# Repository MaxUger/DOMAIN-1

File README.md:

# DOMAIN-1
 Full size keyboard with two additional upper rows.
 
 Main Board:

Daughter Board / Upper Board:

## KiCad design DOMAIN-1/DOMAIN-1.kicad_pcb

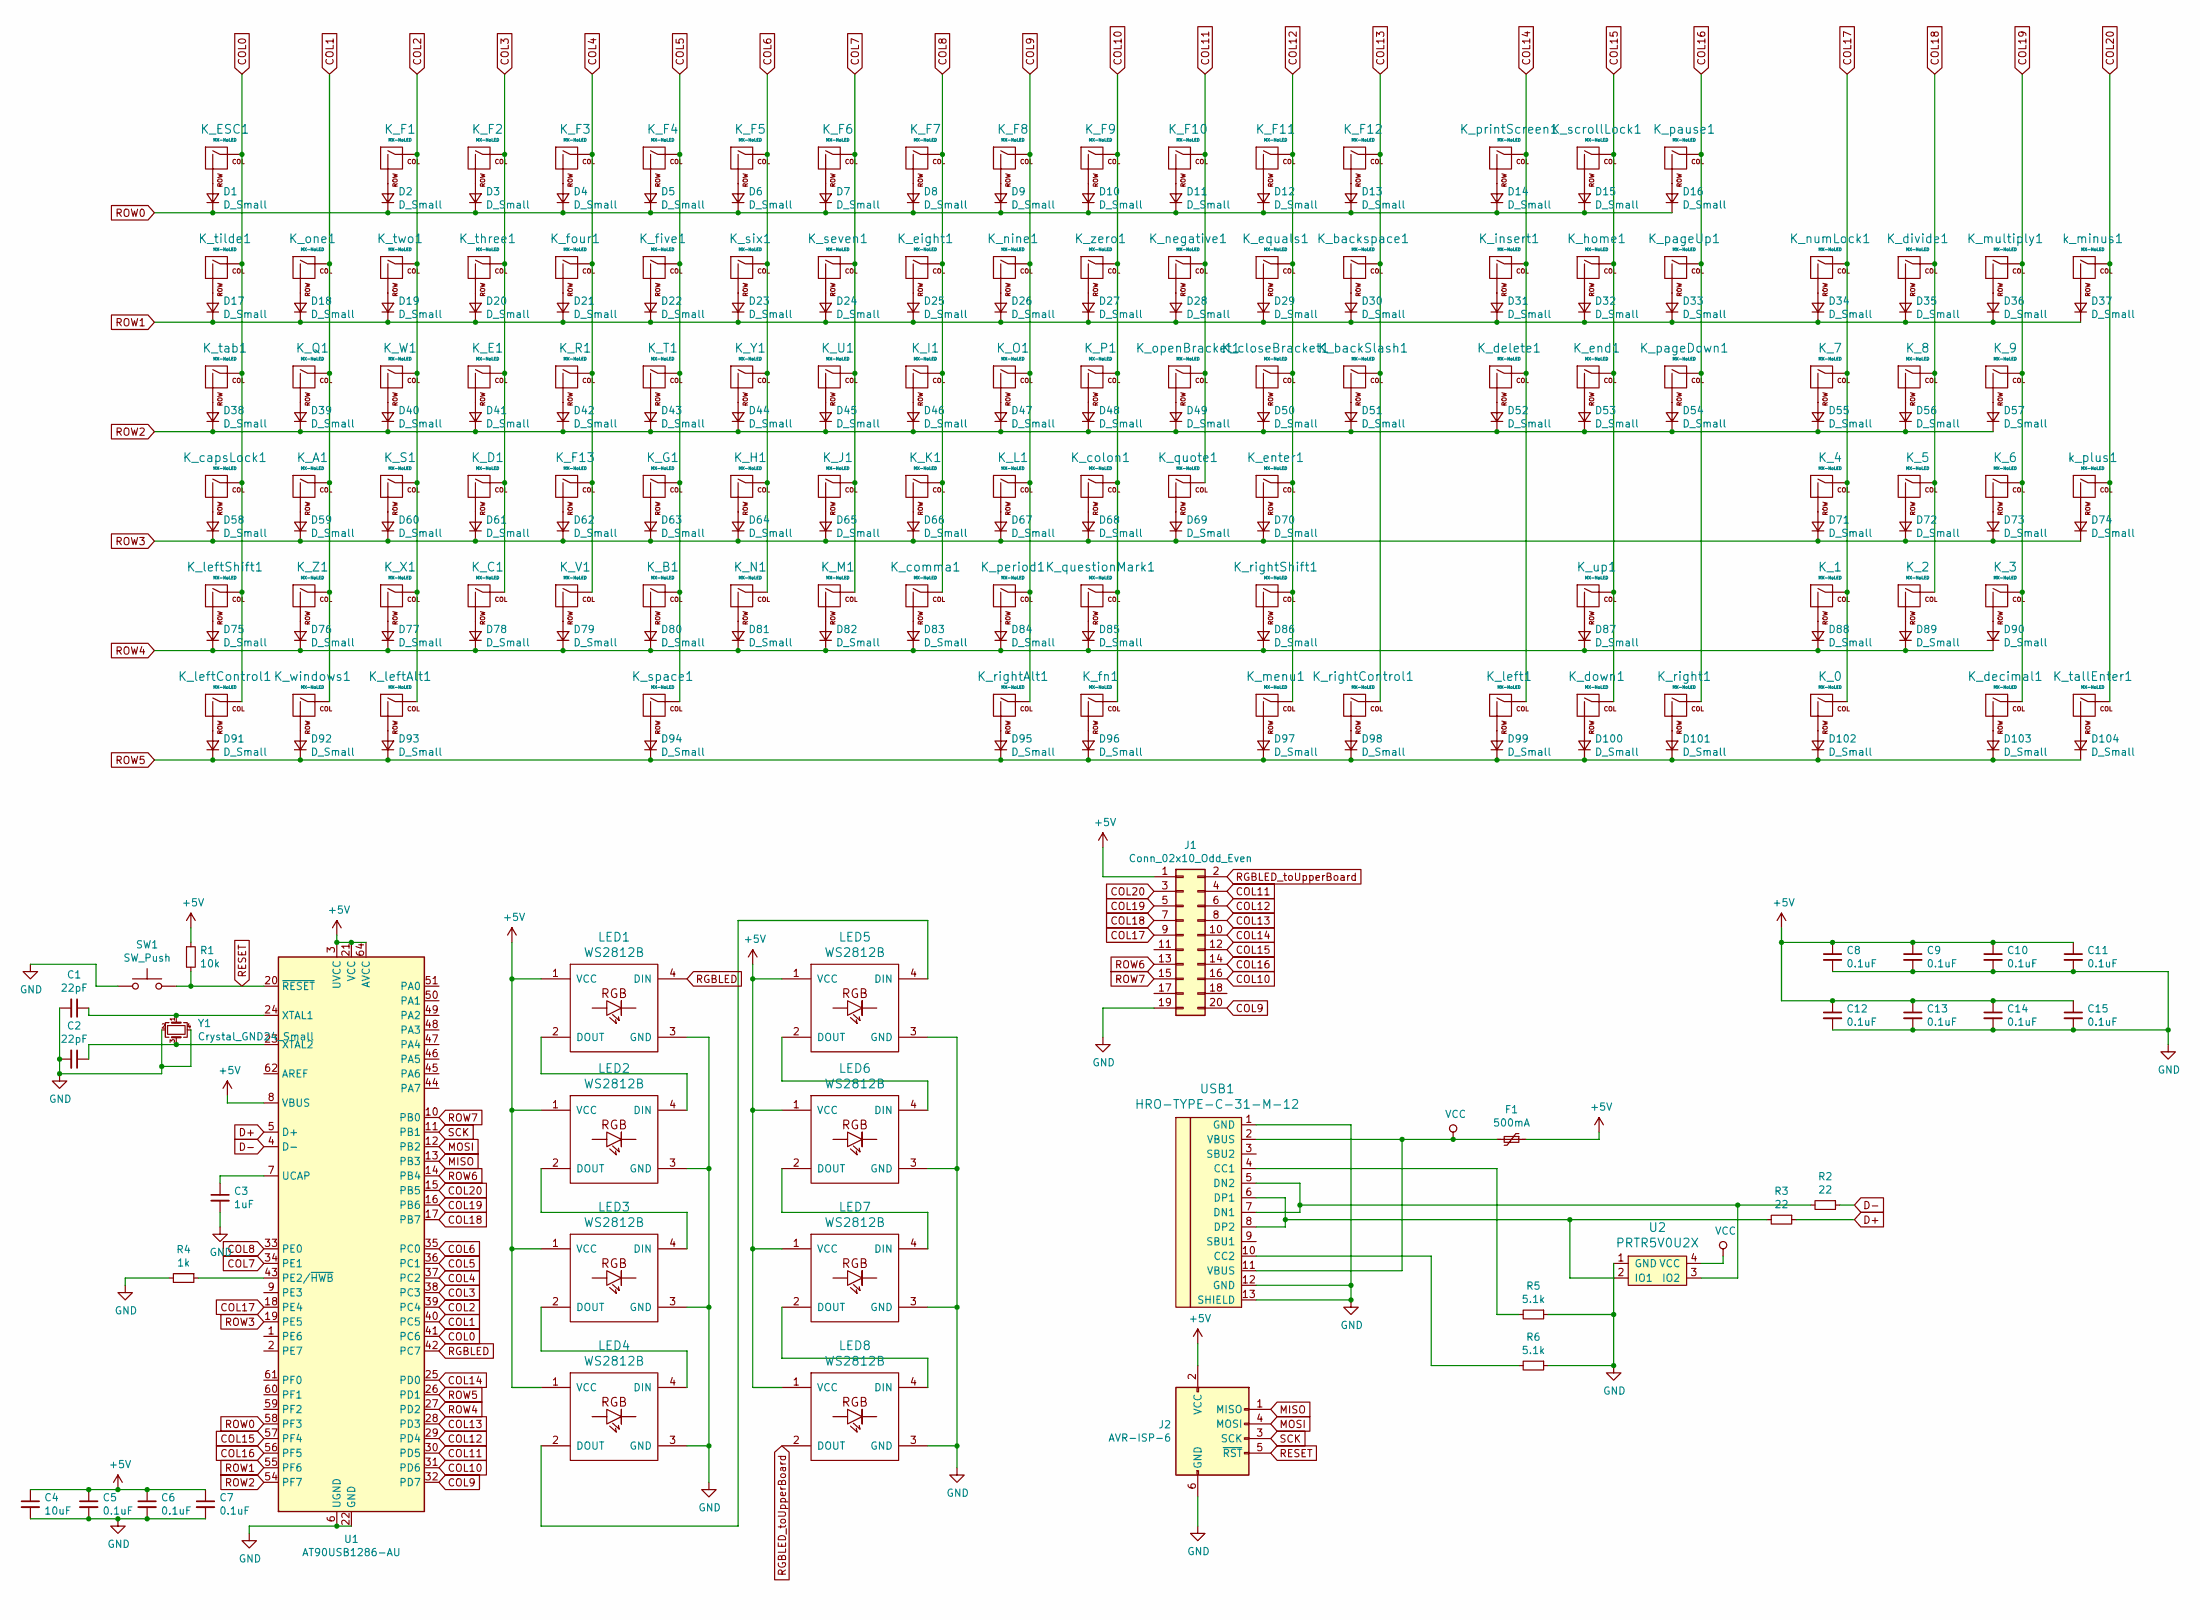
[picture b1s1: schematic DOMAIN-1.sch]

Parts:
C1, C2: 22pF; C_0603_1608Metric
C3: 1uF; C_0603_1608Metric
C4: 10uF; C_0603_1608Metric
C5, C6, C7, C8, C9, C10, C11, C12, C13, C14, C15: 0.1uF; C_0603_1608Metric
D1, D2, D3, D4, D5, D6, D7, D8, D9, D10, D11, D12, D13, D14, D15, D16, D17, D18, D19, D20, D21, D22, D23, D24, D25, D26, D27, D28, D29, D30, D31, D32, D33, D34, D35, D36, D37, D38, D39, D40, D41, D42, D43, D44, D45, D46, D47, D48, D49, D50, D51, D52, D53, D54, D55, D56, D57, D58, D59, D60, D61, D62, D63, D64, D65, D66, D67, D68, D69, D70, D71, D72, D73, D74, D75, D76, D77, D78, D79, D80, D81, D82, D83, D84, D85, D86, D87, D88, D89, D90, D91, D92, D93, D94, D95, D96, D97, D98, D99, D100, D101, D102, D103, D104: D_Small; D_SOD-123
F1: 500mA; Fuse_1206_3216Metric
J1: Conn_02x10_Odd_Even; IDC-Header_2x10_P2.54mm_Horizontal
J2: AVR-ISP-6; Reset_Pretty-Mask
K_0: MX-NoLED; MXOnly-2U-Hotswap
K_1, K_2, K_3, K_4, K_5, K_6, K_7, K_8, K_9: MX-NoLED; MXOnly-1U-Hotswap
K_A1: MX-NoLED; MXOnly-1U-Hotswap
K_B1: MX-NoLED; MXOnly-1U-Hotswap
K_C1: MX-NoLED; MXOnly-1U-Hotswap
K_D1: MX-NoLED; MXOnly-1U-Hotswap
K_E1: MX-NoLED; MXOnly-1U-Hotswap
K_ESC1: MX-NoLED; MXOnly-1U-Hotswap
K_F1, K_F2, K_F3, K_F4, K_F5, K_F6, K_F7, K_F8, K_F9, K_F10, K_F11, K_F12, K_F13: MX-NoLED; MXOnly-1U-Hotswap
K_G1: MX-NoLED; MXOnly-1U-Hotswap
K_H1: MX-NoLED; MXOnly-1U-Hotswap
K_I1: MX-NoLED; MXOnly-1U-Hotswap
K_J1: MX-NoLED; MXOnly-1U-Hotswap
K_K1: MX-NoLED; MXOnly-1U-Hotswap
K_L1: MX-NoLED; MXOnly-1U-Hotswap
K_M1: MX-NoLED; MXOnly-1U-Hotswap
K_N1: MX-NoLED; MXOnly-1U-Hotswap
K_O1: MX-NoLED; MXOnly-1U-Hotswap
K_P1: MX-NoLED; MXOnly-1U-Hotswap
K_Q1: MX-NoLED; MXOnly-1U-Hotswap
K_R1: MX-NoLED; MXOnly-1U-Hotswap
K_S1: MX-NoLED; MXOnly-1U-Hotswap
K_T1: MX-NoLED; MXOnly-1U-Hotswap
K_U1: MX-NoLED; MXOnly-1U-Hotswap
K_V1: MX-NoLED; MXOnly-1U-Hotswap
K_W1: MX-NoLED; MXOnly-1U-Hotswap
K_X1: MX-NoLED; MXOnly-1U-Hotswap
K_Y1: MX-NoLED; MXOnly-1U-Hotswap
K_Z1: MX-NoLED; MXOnly-1U-Hotswap
K_backSlash1: MX-NoLED; MXOnly-1.5U-Hotswap
K_backspace1: MX-NoLED; MXOnly-2U-Hotswap
K_capsLock1: MX-NoLED; MXOnly-1.75U-Hotswap
K_closeBracket1: MX-NoLED; MXOnly-1U-Hotswap
K_colon1: MX-NoLED; MXOnly-1U-Hotswap
K_comma1: MX-NoLED; MXOnly-1U-Hotswap
K_decimal1: MX-NoLED; MXOnly-1U-Hotswap
K_delete1: MX-NoLED; MXOnly-1U-Hotswap
K_divide1: MX-NoLED; MXOnly-1U-Hotswap
K_down1: MX-NoLED; MXOnly-1U-Hotswap
K_eight1: MX-NoLED; MXOnly-1U-Hotswap
K_end1: MX-NoLED; MXOnly-1U-Hotswap
K_enter1: MX-NoLED; MXOnly-2.25U-Hotswap
K_equals1: MX-NoLED; MXOnly-1U-Hotswap
K_five1: MX-NoLED; MXOnly-1U-Hotswap
K_fn1: MX-NoLED; MXOnly-1.25U-Hotswap
K_four1: MX-NoLED; MXOnly-1U-Hotswap
K_home1: MX-NoLED; MXOnly-1U-Hotswap
K_insert1: MX-NoLED; MXOnly-1U-Hotswap
K_left1: MX-NoLED; MXOnly-1U-Hotswap
K_leftAlt1: MX-NoLED; MXOnly-1.25U-Hotswap
K_leftControl1: MX-NoLED; MXOnly-1.25U-Hotswap
K_leftShift1: MX-NoLED; MXOnly-2.25U-Hotswap
K_menu1: MX-NoLED; MXOnly-1.25U-Hotswap
K_multiply1: MX-NoLED; MXOnly-1U-Hotswap
K_negative1: MX-NoLED; MXOnly-1U-Hotswap
K_nine1: MX-NoLED; MXOnly-1U-Hotswap
K_numLock1: MX-NoLED; MXOnly-1U-Hotswap
K_one1: MX-NoLED; MXOnly-1U-Hotswap
K_openBracket1: MX-NoLED; MXOnly-1U-Hotswap
K_pageDown1: MX-NoLED; MXOnly-1U-Hotswap
K_pageUp1: MX-NoLED; MXOnly-1U-Hotswap
K_pause1: MX-NoLED; MXOnly-1U-Hotswap
K_period1: MX-NoLED; MXOnly-1U-Hotswap
K_printScreen1: MX-NoLED; MXOnly-1U-Hotswap
K_questionMark1: MX-NoLED; MXOnly-1U-Hotswap
K_quote1: MX-NoLED; MXOnly-1U-Hotswap
K_right1: MX-NoLED; MXOnly-1U-Hotswap
K_rightAlt1: MX-NoLED; MXOnly-1.25U-Hotswap
K_rightControl1: MX-NoLED; MXOnly-1.25U-Hotswap
K_rightShift1: MX-NoLED; MXOnly-2.75U-Hotswap
K_scrollLock1: MX-NoLED; MXOnly-1U-Hotswap
K_seven1: MX-NoLED; MXOnly-1U-Hotswap
K_six1: MX-NoLED; MXOnly-1U-Hotswap
K_space1: MX-NoLED; MXOnly-6.25U-Hotswap
K_tab1: MX-NoLED; MXOnly-1.5U-Hotswap
K_tallEnter1: MX-NoLED; MX-2U-Hotswap-Vertical
K_three1: MX-NoLED; MXOnly-1U-Hotswap
K_tilde1: MX-NoLED; MXOnly-1U-Hotswap
K_two1: MX-NoLED; MXOnly-1U-Hotswap
K_up1: MX-NoLED; MXOnly-1U-Hotswap
K_windows1: MX-NoLED; MXOnly-1.25U-Hotswap
K_zero1: MX-NoLED; MXOnly-1U-Hotswap
LED1, LED2, LED3, LED4, LED5, LED6, LED7, LED8: WS2812B
R1: 10k; R_0805_2012Metric
R2, R3: 22; R_0805_2012Metric
R4: 1k; R_0805_2012Metric
R5, R6: 5.1k; R_0805_2012Metric
SW1: SW_Push; SKQG-1155865
U1: AT90USB1286-AU; TQFP-64_14x14mm_P0.8mm
U2: PRTR5V0U2X; SOT143B
USB1: HRO-TYPE-C-31-M-12; HRO-TYPE-C-31-M-12-Assembly
Y1: Crystal_GND24_Small; Crystal_SMD_3225-4Pin_3.2x2.5mm
k_minus1: MX-NoLED; MXOnly-1U-Hotswap
k_plus1: MX-NoLED; MX-2U-Hotswap-Vertical

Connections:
+5V: C4.1, C5.1, C6.1, C7.1, C8.1, C9.1, C10.1, C11.1, C12.1, C13.1, C14.1, C15.1, F1.1, J1.1, J2.2 (VCC), LED1.1 (VCC), LED2.1 (VCC), LED3.1 (VCC), LED4.1 (VCC), LED5.1 (VCC), LED6.1 (VCC), LED7.1 (VCC), LED8.1 (VCC), R1.1, U1.3 (UVCC), U1.8 (VBUS), U1.21 (VCC), U1.52 (VCC), U1.64 (AVCC)
COL0: K_ESC1.1 (COL), K_capsLock1.1 (COL), K_leftControl1.1 (COL), K_leftShift1.1 (COL), K_tab1.1 (COL), K_tilde1.1 (COL), U1.41 (PC6)
COL1: K_A1.1 (COL), K_Q1.1 (COL), K_Z1.1 (COL), K_one1.1 (COL), K_windows1.1 (COL), U1.40 (PC5)
COL2: K_F1.1 (COL), K_S1.1 (COL), K_W1.1 (COL), K_X1.1 (COL), K_leftAlt1.1 (COL), K_two1.1 (COL), U1.39 (PC4)
COL3: K_C1.1 (COL), K_D1.1 (COL), K_E1.1 (COL), K_F2.1 (COL), K_three1.1 (COL), U1.38 (PC3)
COL4: K_F3.1 (COL), K_F13.1 (COL), K_R1.1 (COL), K_V1.1 (COL), K_four1.1 (COL), U1.37 (PC2)
COL5: K_B1.1 (COL), K_F4.1 (COL), K_G1.1 (COL), K_T1.1 (COL), K_five1.1 (COL), K_space1.1 (COL), U1.36 (PC1)
COL6: K_F5.1 (COL), K_H1.1 (COL), K_N1.1 (COL), K_Y1.1 (COL), K_six1.1 (COL), U1.35 (PC0)
COL7: K_F6.1 (COL), K_J1.1 (COL), K_M1.1 (COL), K_U1.1 (COL), K_seven1.1 (COL), U1.34 (PE1)
COL8: K_F7.1 (COL), K_I1.1 (COL), K_K1.1 (COL), K_comma1.1 (COL), K_eight1.1 (COL), U1.33 (PE0)
COL9: J1.20, K_F8.1 (COL), K_L1.1 (COL), K_O1.1 (COL), K_nine1.1 (COL), K_period1.1 (COL), K_rightAlt1.1 (COL), U1.32 (PD7)
COL10: J1.16, K_F9.1 (COL), K_P1.1 (COL), K_colon1.1 (COL), K_fn1.1 (COL), K_questionMark1.1 (COL), K_zero1.1 (COL), U1.31 (PD6)
COL11: J1.4, K_F10.1 (COL), K_negative1.1 (COL), K_openBracket1.1 (COL), K_quote1.1 (COL), U1.30 (PD5)
COL12: J1.6, K_F11.1 (COL), K_closeBracket1.1 (COL), K_enter1.1 (COL), K_equals1.1 (COL), K_menu1.1 (COL), K_rightShift1.1 (COL), U1.29 (PD4)
COL13: J1.8, K_F12.1 (COL), K_backSlash1.1 (COL), K_backspace1.1 (COL), K_rightControl1.1 (COL), U1.28 (PD3)
COL14: J1.10, K_delete1.1 (COL), K_insert1.1 (COL), K_left1.1 (COL), K_printScreen1.1 (COL), U1.25 (PD0)
COL15: J1.12, K_down1.1 (COL), K_end1.1 (COL), K_home1.1 (COL), K_scrollLock1.1 (COL), K_up1.1 (COL), U1.57 (PF4)
COL16: J1.14, K_pageDown1.1 (COL), K_pageUp1.1 (COL), K_pause1.1 (COL), K_right1.1 (COL), U1.56 (PF5)
COL17: J1.9, K_0.1 (COL), K_1.1 (COL), K_4.1 (COL), K_7.1 (COL), K_numLock1.1 (COL), U1.18 (PE4)
COL18: J1.7, K_2.1 (COL), K_5.1 (COL), K_8.1 (COL), K_divide1.1 (COL), U1.17 (PB7)
COL19: J1.5, K_3.1 (COL), K_6.1 (COL), K_9.1 (COL), K_decimal1.1 (COL), K_multiply1.1 (COL), U1.16 (PB6)
COL20: J1.3, K_tallEnter1.1 (COL), U1.15 (PB5), k_minus1.1 (COL), k_plus1.1 (COL)
D+: R3.1, U1.5 (D+)
D-: R2.1, U1.4 (D-)
GND: C1.2, C2.2, C3.2, C4.2, C5.2, C6.2, C7.2, C8.2, C9.2, C10.2, C11.2, C12.2, C13.2, C14.2, C15.2, J1.19, J2.6 (GND), LED1.3 (GND), LED2.3 (GND), LED3.3 (GND), LED4.3 (GND), LED5.3 (GND), LED6.3 (GND), LED7.3 (GND), LED8.3 (GND), R4.2, R5.1, R6.1, SW1.1, U1.6 (UGND), U1.22 (GND), U1.53 (GND), U1.63 (GND), U2.1 (GND), USB1.1 (GND), USB1.12 (GND), USB1.13 (SHIELD), Y1.2, Y1.4
MISO: J2.1 (MISO), U1.13 (PB3)
MOSI: J2.4 (MOSI), U1.12 (PB2)
unnamed: C1.1, U1.24 (XTAL1), Y1.1
unnamed: C2.1, U1.23 (XTAL2), Y1.3
unnamed: C3.1, U1.7 (UCAP)
unnamed: D1.2 (A), K_ESC1.2 (ROW)
unnamed: D2.2 (A), K_F1.2 (ROW)
unnamed: D3.2 (A), K_F2.2 (ROW)
unnamed: D4.2 (A), K_F3.2 (ROW)
unnamed: D5.2 (A), K_F4.2 (ROW)
unnamed: D6.2 (A), K_F5.2 (ROW)
unnamed: D7.2 (A), K_F6.2 (ROW)
unnamed: D8.2 (A), K_F7.2 (ROW)
unnamed: D9.2 (A), K_F8.2 (ROW)
unnamed: D10.2 (A), K_F9.2 (ROW)
unnamed: D11.2 (A), K_F10.2 (ROW)
unnamed: D12.2 (A), K_F11.2 (ROW)
unnamed: D13.2 (A), K_F12.2 (ROW)
unnamed: D14.2 (A), K_printScreen1.2 (ROW)
unnamed: D15.2 (A), K_scrollLock1.2 (ROW)
unnamed: D16.2 (A), K_pause1.2 (ROW)
unnamed: D17.2 (A), K_tilde1.2 (ROW)
unnamed: D18.2 (A), K_one1.2 (ROW)
unnamed: D19.2 (A), K_two1.2 (ROW)
unnamed: D20.2 (A), K_three1.2 (ROW)
unnamed: D21.2 (A), K_four1.2 (ROW)
unnamed: D22.2 (A), K_five1.2 (ROW)
unnamed: D23.2 (A), K_six1.2 (ROW)
unnamed: D24.2 (A), K_seven1.2 (ROW)
unnamed: D25.2 (A), K_eight1.2 (ROW)
unnamed: D26.2 (A), K_nine1.2 (ROW)
unnamed: D27.2 (A), K_zero1.2 (ROW)
unnamed: D28.2 (A), K_negative1.2 (ROW)
unnamed: D29.2 (A), K_equals1.2 (ROW)
unnamed: D30.2 (A), K_backspace1.2 (ROW)
unnamed: D31.2 (A), K_insert1.2 (ROW)
unnamed: D32.2 (A), K_home1.2 (ROW)
unnamed: D33.2 (A), K_pageUp1.2 (ROW)
unnamed: D34.2 (A), K_numLock1.2 (ROW)
unnamed: D35.2 (A), K_divide1.2 (ROW)
unnamed: D36.2 (A), K_multiply1.2 (ROW)
unnamed: D37.2 (A), k_minus1.2 (ROW)
unnamed: D38.2 (A), K_tab1.2 (ROW)
unnamed: D39.2 (A), K_Q1.2 (ROW)
unnamed: D40.2 (A), K_W1.2 (ROW)
unnamed: D41.2 (A), K_E1.2 (ROW)
unnamed: D42.2 (A), K_R1.2 (ROW)
unnamed: D43.2 (A), K_T1.2 (ROW)
unnamed: D44.2 (A), K_Y1.2 (ROW)
unnamed: D45.2 (A), K_U1.2 (ROW)
unnamed: D46.2 (A), K_I1.2 (ROW)
unnamed: D47.2 (A), K_O1.2 (ROW)
unnamed: D48.2 (A), K_P1.2 (ROW)
unnamed: D49.2 (A), K_openBracket1.2 (ROW)
unnamed: D50.2 (A), K_closeBracket1.2 (ROW)
unnamed: D51.2 (A), K_backSlash1.2 (ROW)
unnamed: D52.2 (A), K_delete1.2 (ROW)
unnamed: D53.2 (A), K_end1.2 (ROW)
unnamed: D54.2 (A), K_pageDown1.2 (ROW)
unnamed: D55.2 (A), K_7.2 (ROW)
unnamed: D56.2 (A), K_8.2 (ROW)
unnamed: D57.2 (A), K_9.2 (ROW)
unnamed: D58.2 (A), K_capsLock1.2 (ROW)
unnamed: D59.2 (A), K_A1.2 (ROW)
unnamed: D60.2 (A), K_S1.2 (ROW)
unnamed: D61.2 (A), K_D1.2 (ROW)
unnamed: D62.2 (A), K_F13.2 (ROW)
unnamed: D63.2 (A), K_G1.2 (ROW)
unnamed: D64.2 (A), K_H1.2 (ROW)
unnamed: D65.2 (A), K_J1.2 (ROW)
unnamed: D66.2 (A), K_K1.2 (ROW)
unnamed: D67.2 (A), K_L1.2 (ROW)
unnamed: D68.2 (A), K_colon1.2 (ROW)
unnamed: D69.2 (A), K_quote1.2 (ROW)
unnamed: D70.2 (A), K_enter1.2 (ROW)
unnamed: D71.2 (A), K_4.2 (ROW)
unnamed: D72.2 (A), K_5.2 (ROW)
unnamed: D73.2 (A), K_6.2 (ROW)
unnamed: D74.2 (A), k_plus1.2 (ROW)
unnamed: D75.2 (A), K_leftShift1.2 (ROW)
unnamed: D76.2 (A), K_Z1.2 (ROW)
unnamed: D77.2 (A), K_X1.2 (ROW)
unnamed: D78.2 (A), K_C1.2 (ROW)
unnamed: D79.2 (A), K_V1.2 (ROW)
unnamed: D80.2 (A), K_B1.2 (ROW)
unnamed: D81.2 (A), K_N1.2 (ROW)
unnamed: D82.2 (A), K_M1.2 (ROW)
unnamed: D83.2 (A), K_comma1.2 (ROW)
unnamed: D84.2 (A), K_period1.2 (ROW)
unnamed: D85.2 (A), K_questionMark1.2 (ROW)
unnamed: D86.2 (A), K_rightShift1.2 (ROW)
unnamed: D87.2 (A), K_up1.2 (ROW)
unnamed: D88.2 (A), K_1.2 (ROW)
unnamed: D89.2 (A), K_2.2 (ROW)
unnamed: D90.2 (A), K_3.2 (ROW)
unnamed: D91.2 (A), K_leftControl1.2 (ROW)
unnamed: D92.2 (A), K_windows1.2 (ROW)
unnamed: D93.2 (A), K_leftAlt1.2 (ROW)
unnamed: D94.2 (A), K_space1.2 (ROW)
unnamed: D95.2 (A), K_rightAlt1.2 (ROW)
unnamed: D96.2 (A), K_fn1.2 (ROW)
unnamed: D97.2 (A), K_menu1.2 (ROW)
unnamed: D98.2 (A), K_rightControl1.2 (ROW)
unnamed: D99.2 (A), K_left1.2 (ROW)
unnamed: D100.2 (A), K_down1.2 (ROW)
unnamed: D101.2 (A), K_right1.2 (ROW)
unnamed: D102.2 (A), K_0.2 (ROW)
unnamed: D103.2 (A), K_decimal1.2 (ROW)
unnamed: D104.2 (A), K_tallEnter1.2 (ROW)
unnamed: LED1.2 (DOUT), LED2.4 (DIN)
unnamed: LED2.2 (DOUT), LED3.4 (DIN)
unnamed: LED3.2 (DOUT), LED4.4 (DIN)
unnamed: LED4.2 (DOUT), LED5.4 (DIN)
unnamed: LED5.2 (DOUT), LED6.4 (DIN)
unnamed: LED6.2 (DOUT), LED7.4 (DIN)
unnamed: LED7.2 (DOUT), LED8.4 (DIN)
unnamed: R2.2, U2.3 (IO2), USB1.5 (DN2), USB1.7 (DN1)
unnamed: R3.2, U2.2 (IO1), USB1.6 (DP1), USB1.8 (DP2)
unnamed: R4.1, U1.43 (PE2/~HWB)
unnamed: R5.2, USB1.4 (CC1)
unnamed: R6.2, USB1.10 (CC2)
RESET: J2.5 (~RST), R1.2, SW1.2, U1.20 (~RESET)
RGBLED: LED1.4 (DIN), U1.42 (PC7)
RGBLED_toUpperBoard: J1.2, LED8.2 (DOUT)
ROW0: D1.1 (K), D2.1 (K), D3.1 (K), D4.1 (K), D5.1 (K), D6.1 (K), D7.1 (K), D8.1 (K), D9.1 (K), D10.1 (K), D11.1 (K), D12.1 (K), D13.1 (K), D14.1 (K), D15.1 (K), D16.1 (K), U1.58 (PF3)
ROW1: D17.1 (K), D18.1 (K), D19.1 (K), D20.1 (K), D21.1 (K), D22.1 (K), D23.1 (K), D24.1 (K), D25.1 (K), D26.1 (K), D27.1 (K), D28.1 (K), D29.1 (K), D30.1 (K), D31.1 (K), D32.1 (K), D33.1 (K), D34.1 (K), D35.1 (K), D36.1 (K), D37.1 (K), U1.55 (PF6)
ROW2: D38.1 (K), D39.1 (K), D40.1 (K), D41.1 (K), D42.1 (K), D43.1 (K), D44.1 (K), D45.1 (K), D46.1 (K), D47.1 (K), D48.1 (K), D49.1 (K), D50.1 (K), D51.1 (K), D52.1 (K), D53.1 (K), D54.1 (K), D55.1 (K), D56.1 (K), D57.1 (K), U1.54 (PF7)
ROW3: D58.1 (K), D59.1 (K), D60.1 (K), D61.1 (K), D62.1 (K), D63.1 (K), D64.1 (K), D65.1 (K), D66.1 (K), D67.1 (K), D68.1 (K), D69.1 (K), D70.1 (K), D71.1 (K), D72.1 (K), D73.1 (K), D74.1 (K), U1.19 (PE5)
ROW4: D75.1 (K), D76.1 (K), D77.1 (K), D78.1 (K), D79.1 (K), D80.1 (K), D81.1 (K), D82.1 (K), D83.1 (K), D84.1 (K), D85.1 (K), D86.1 (K), D87.1 (K), D88.1 (K), D89.1 (K), D90.1 (K), U1.27 (PD2)
ROW5: D91.1 (K), D92.1 (K), D93.1 (K), D94.1 (K), D95.1 (K), D96.1 (K), D97.1 (K), D98.1 (K), D99.1 (K), D100.1 (K), D101.1 (K), D102.1 (K), D103.1 (K), D104.1 (K), U1.26 (PD1)
ROW6: J1.13, U1.14 (PB4)
ROW7: J1.15, U1.10 (PB0)
SCK: J2.3 (SCK), U1.11 (PB1)
VCC: F1.2, U2.4 (VCC), USB1.2 (VBUS), USB1.11 (VBUS)

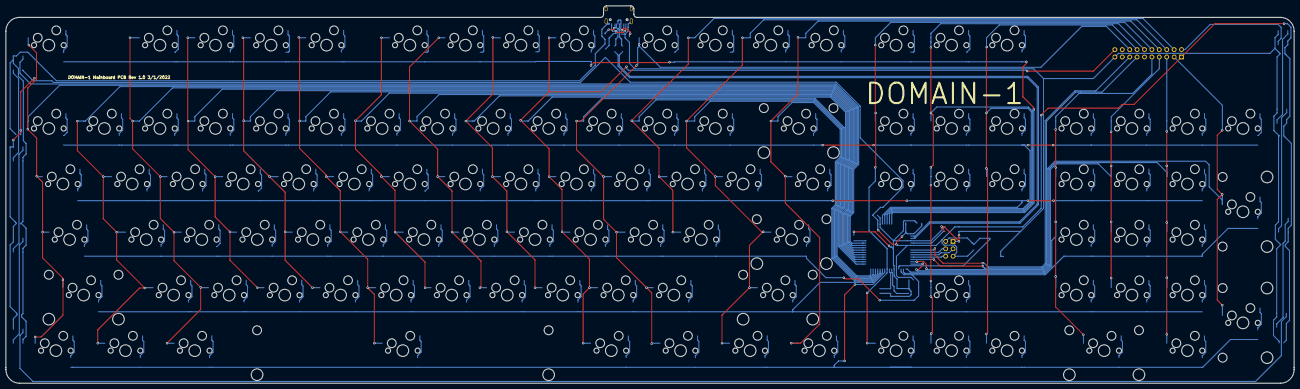
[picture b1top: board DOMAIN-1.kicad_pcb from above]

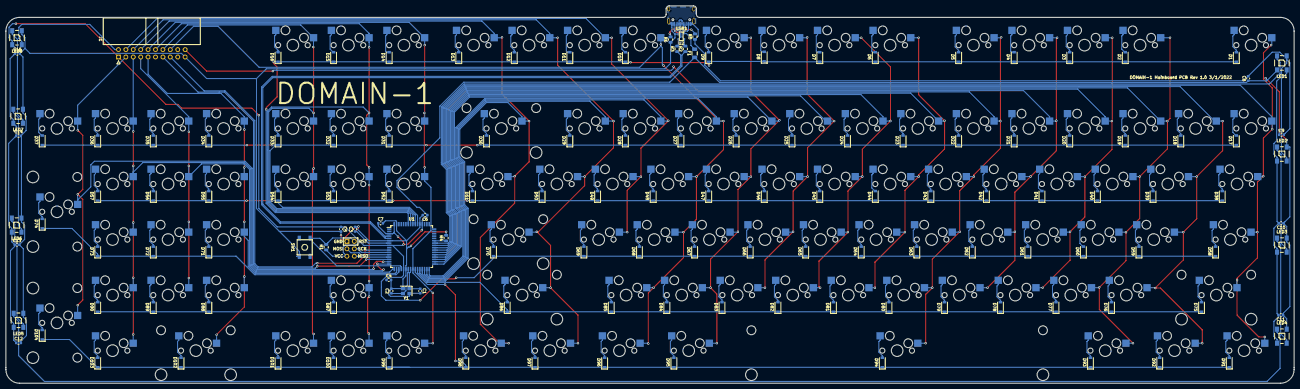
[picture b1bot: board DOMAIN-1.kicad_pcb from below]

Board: 2 copper layers, 441.8 x 129.4 mm, 245 parts (141 on the bottom side), 159 nets.

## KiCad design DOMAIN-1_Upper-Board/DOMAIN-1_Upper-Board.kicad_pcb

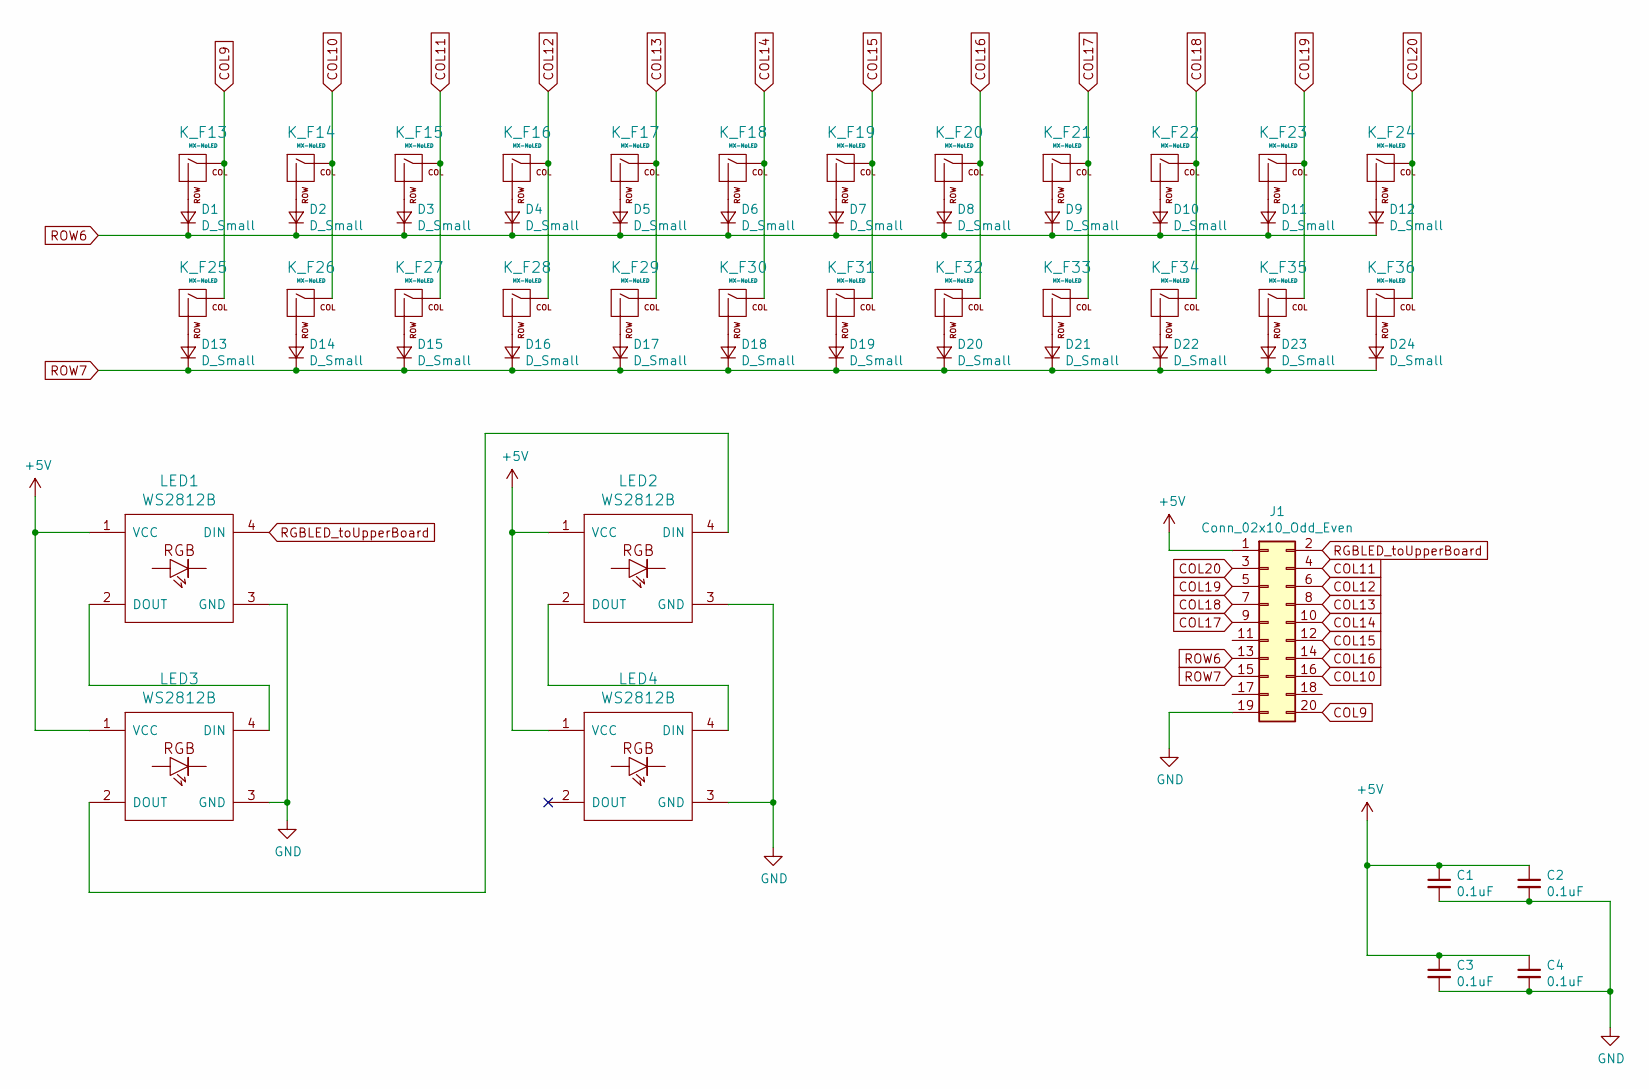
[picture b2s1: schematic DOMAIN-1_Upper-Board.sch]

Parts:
C1, C2, C3, C4: 0.1uF; C_0603_1608Metric
D1, D2, D3, D4, D5, D6, D7, D8, D9, D10, D11, D12, D13, D14, D15, D16, D17, D18, D19, D20, D21, D22, D23, D24: D_Small; D_SOD-123
J1: Conn_02x10_Odd_Even; IDC-Header_2x10_P2.54mm_Horizontal
K_F13, K_F14, K_F15, K_F16, K_F17, K_F18, K_F19, K_F20, K_F21, K_F22, K_F23, K_F24, K_F25, K_F26, K_F27, K_F28, K_F29, K_F30, K_F31, K_F32, K_F33, K_F34, K_F35, K_F36: MX-NoLED; MXOnly-1.75U-Hotswap
LED1, LED2, LED3, LED4: WS2812B

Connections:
+5V: C1.1, C2.1, C3.1, C4.1, J1.1, LED1.1 (VCC), LED2.1 (VCC), LED3.1 (VCC), LED4.1 (VCC)
COL9: J1.20, K_F13.1 (COL), K_F25.1 (COL)
COL10: J1.16, K_F14.1 (COL), K_F26.1 (COL)
COL11: J1.4, K_F15.1 (COL), K_F27.1 (COL)
COL12: J1.6, K_F16.1 (COL), K_F28.1 (COL)
COL13: J1.8, K_F17.1 (COL), K_F29.1 (COL)
COL14: J1.10, K_F18.1 (COL), K_F30.1 (COL)
COL15: J1.12, K_F19.1 (COL), K_F31.1 (COL)
COL16: J1.14, K_F20.1 (COL), K_F32.1 (COL)
COL17: J1.9, K_F21.1 (COL), K_F33.1 (COL)
COL18: J1.7, K_F22.1 (COL), K_F34.1 (COL)
COL19: J1.5, K_F23.1 (COL), K_F35.1 (COL)
COL20: J1.3, K_F24.1 (COL), K_F36.1 (COL)
GND: C1.2, C2.2, C3.2, C4.2, J1.19, LED1.3 (GND), LED2.3 (GND), LED3.3 (GND), LED4.3 (GND)
unnamed: D1.2 (A), K_F13.2 (ROW)
unnamed: D2.2 (A), K_F14.2 (ROW)
unnamed: D3.2 (A), K_F15.2 (ROW)
unnamed: D4.2 (A), K_F16.2 (ROW)
unnamed: D5.2 (A), K_F17.2 (ROW)
unnamed: D6.2 (A), K_F18.2 (ROW)
unnamed: D7.2 (A), K_F19.2 (ROW)
unnamed: D8.2 (A), K_F20.2 (ROW)
unnamed: D9.2 (A), K_F21.2 (ROW)
unnamed: D10.2 (A), K_F22.2 (ROW)
unnamed: D11.2 (A), K_F23.2 (ROW)
unnamed: D12.2 (A), K_F24.2 (ROW)
unnamed: D13.2 (A), K_F25.2 (ROW)
unnamed: D14.2 (A), K_F26.2 (ROW)
unnamed: D15.2 (A), K_F27.2 (ROW)
unnamed: D16.2 (A), K_F28.2 (ROW)
unnamed: D17.2 (A), K_F29.2 (ROW)
unnamed: D18.2 (A), K_F30.2 (ROW)
unnamed: D19.2 (A), K_F31.2 (ROW)
unnamed: D20.2 (A), K_F32.2 (ROW)
unnamed: D21.2 (A), K_F33.2 (ROW)
unnamed: D22.2 (A), K_F34.2 (ROW)
unnamed: D23.2 (A), K_F35.2 (ROW)
unnamed: D24.2 (A), K_F36.2 (ROW)
unnamed: LED1.2 (DOUT), LED3.4 (DIN)
unnamed: LED2.2 (DOUT), LED4.4 (DIN)
unnamed: LED2.4 (DIN), LED3.2 (DOUT)
RGBLED_toUpperBoard: J1.2, LED1.4 (DIN)
ROW6: D1.1 (K), D2.1 (K), D3.1 (K), D4.1 (K), D5.1 (K), D6.1 (K), D7.1 (K), D8.1 (K), D9.1 (K), D10.1 (K), D11.1 (K), D12.1 (K), J1.13
ROW7: D13.1 (K), D14.1 (K), D15.1 (K), D16.1 (K), D17.1 (K), D18.1 (K), D19.1 (K), D20.1 (K), D21.1 (K), D22.1 (K), D23.1 (K), D24.1 (K), J1.15

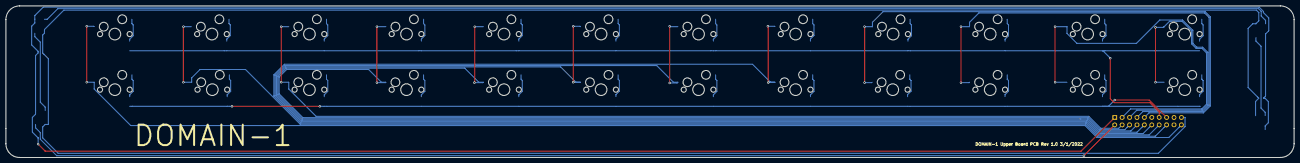
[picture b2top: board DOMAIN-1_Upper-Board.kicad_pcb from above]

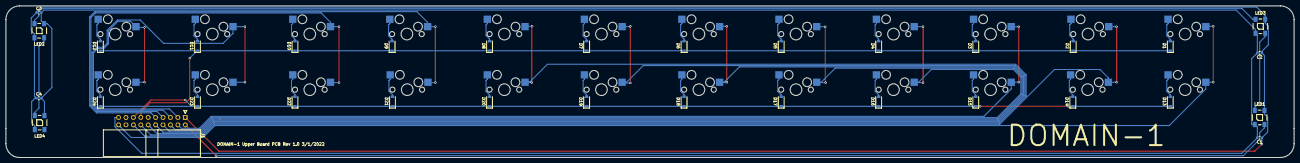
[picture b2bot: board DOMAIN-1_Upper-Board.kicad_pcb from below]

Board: 2 copper layers, 441.5 x 51.9 mm, 57 parts (33 on the bottom side), 44 nets.

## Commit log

2022-01-01 Finished MCU schematic
2022-01-01 Finished matrix
2022-01-02 Finished PCB matrix
2022-01-02 Finished PCB layout
2022-01-02 Finished LED placement
2022-01-03 Finished mainboard
2022-01-03 Finished Upperboard
2022-01-03 Generated gerber files
